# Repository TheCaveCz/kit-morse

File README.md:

# Morseovka

## Česky

Stavebnice morseovky. Zmáčkni tlačítko a pošli zprávu na druhý konec drátu.

* [Návod na stavbu](doc/manual-cz.md) ([PDF](doc/manual-cz.pdf))

## English

Coming soon...

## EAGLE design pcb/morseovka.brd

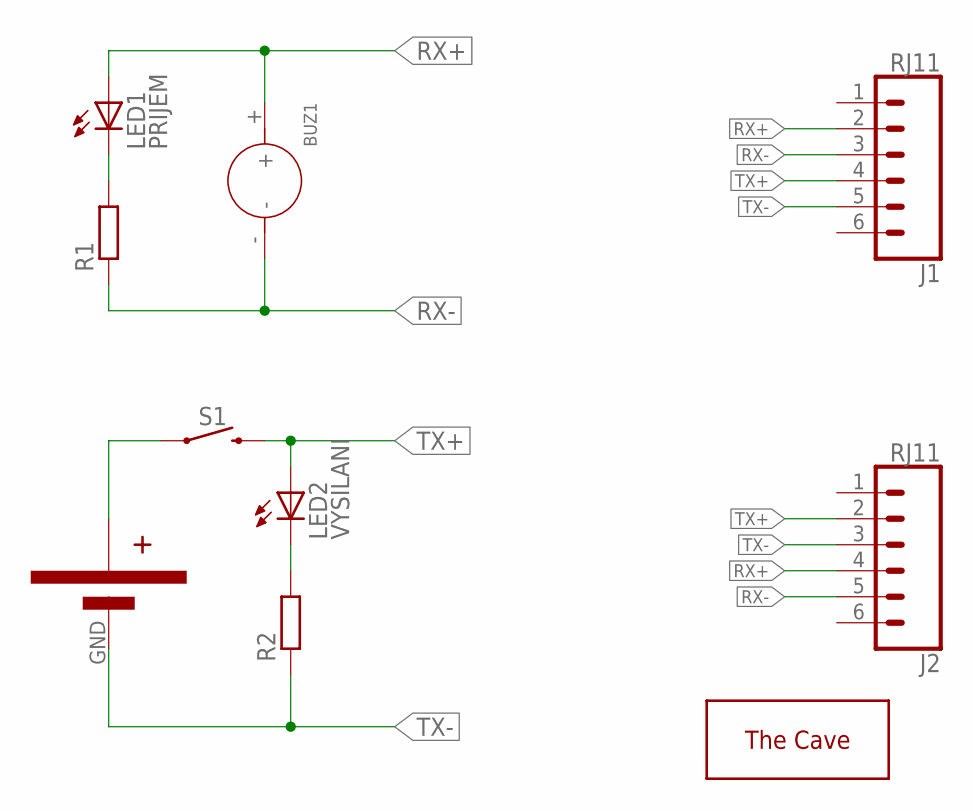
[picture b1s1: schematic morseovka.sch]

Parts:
BUZ1: DIP-BUZZER-3V(KS-12065D03YA); BZ2-7.6-D12.0XH6.5MM
J1, J2: RJ11; RJ11-6
LED1: PRIJEM; LED5MM
LED2: VYSILANI; LED5MM
R1, R2: R-EU_0207/7; 0207/7
S1: MOMENTARY-SWITCH-SPST-PTH-12MM; TACTILE_SWITCH_PTH_12MM
U$1: CR2032HSMD; CR2032H
U$2: THECAVE_LOGO_NEW_TOP; NEW_LOGO_TOP

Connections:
unnamed: LED1.K (C), R1.2
unnamed: S1.1, U$1.VCC.1 (VCC), U$1.VCC.2 (VCC)
unnamed: LED2.K (C), R2.2
RX+: BUZ1.+, J1.2, J2.4, LED1.A
RX-: BUZ1.-, J1.3, J2.5, R1.1
TX+: J1.4, J2.2, LED2.A, S1.3 (2)
TX-: J1.5, J2.3, R2.1, U$1.GND

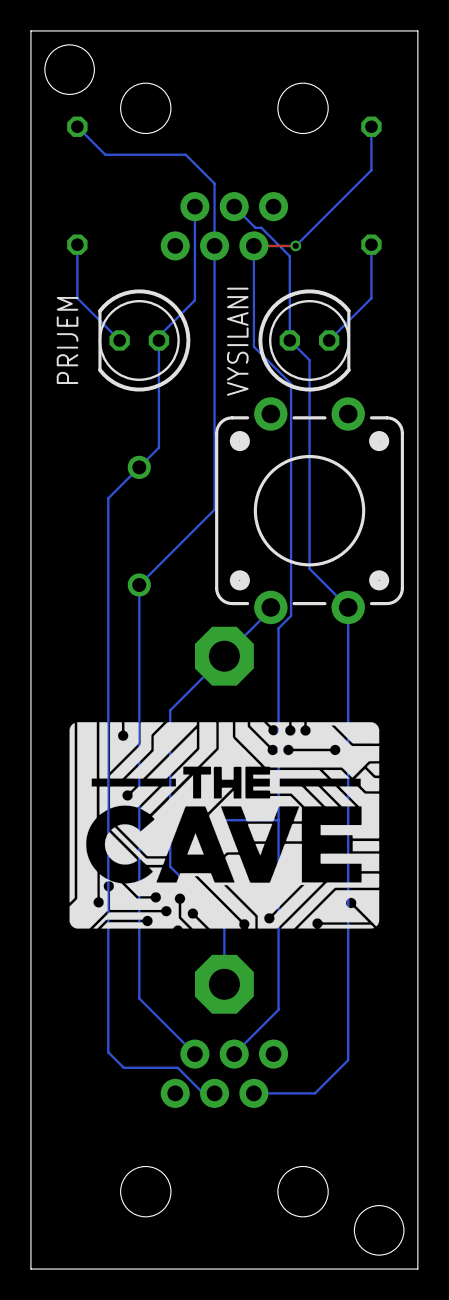
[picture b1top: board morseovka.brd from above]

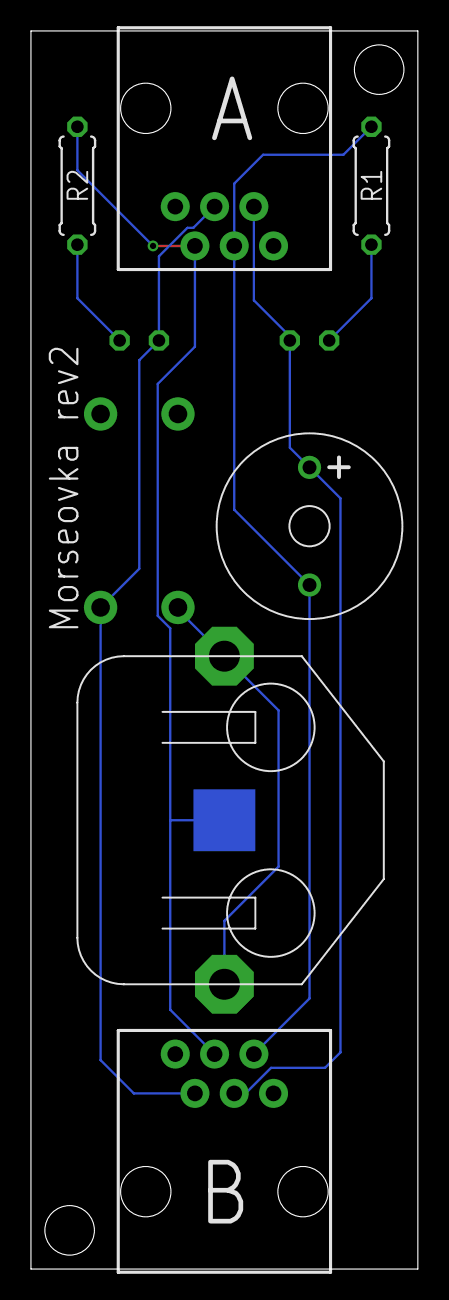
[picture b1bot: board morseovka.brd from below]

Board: 2 copper layers, 25.0 x 80.0 mm, 10 parts (6 on the bottom side), 7 nets.

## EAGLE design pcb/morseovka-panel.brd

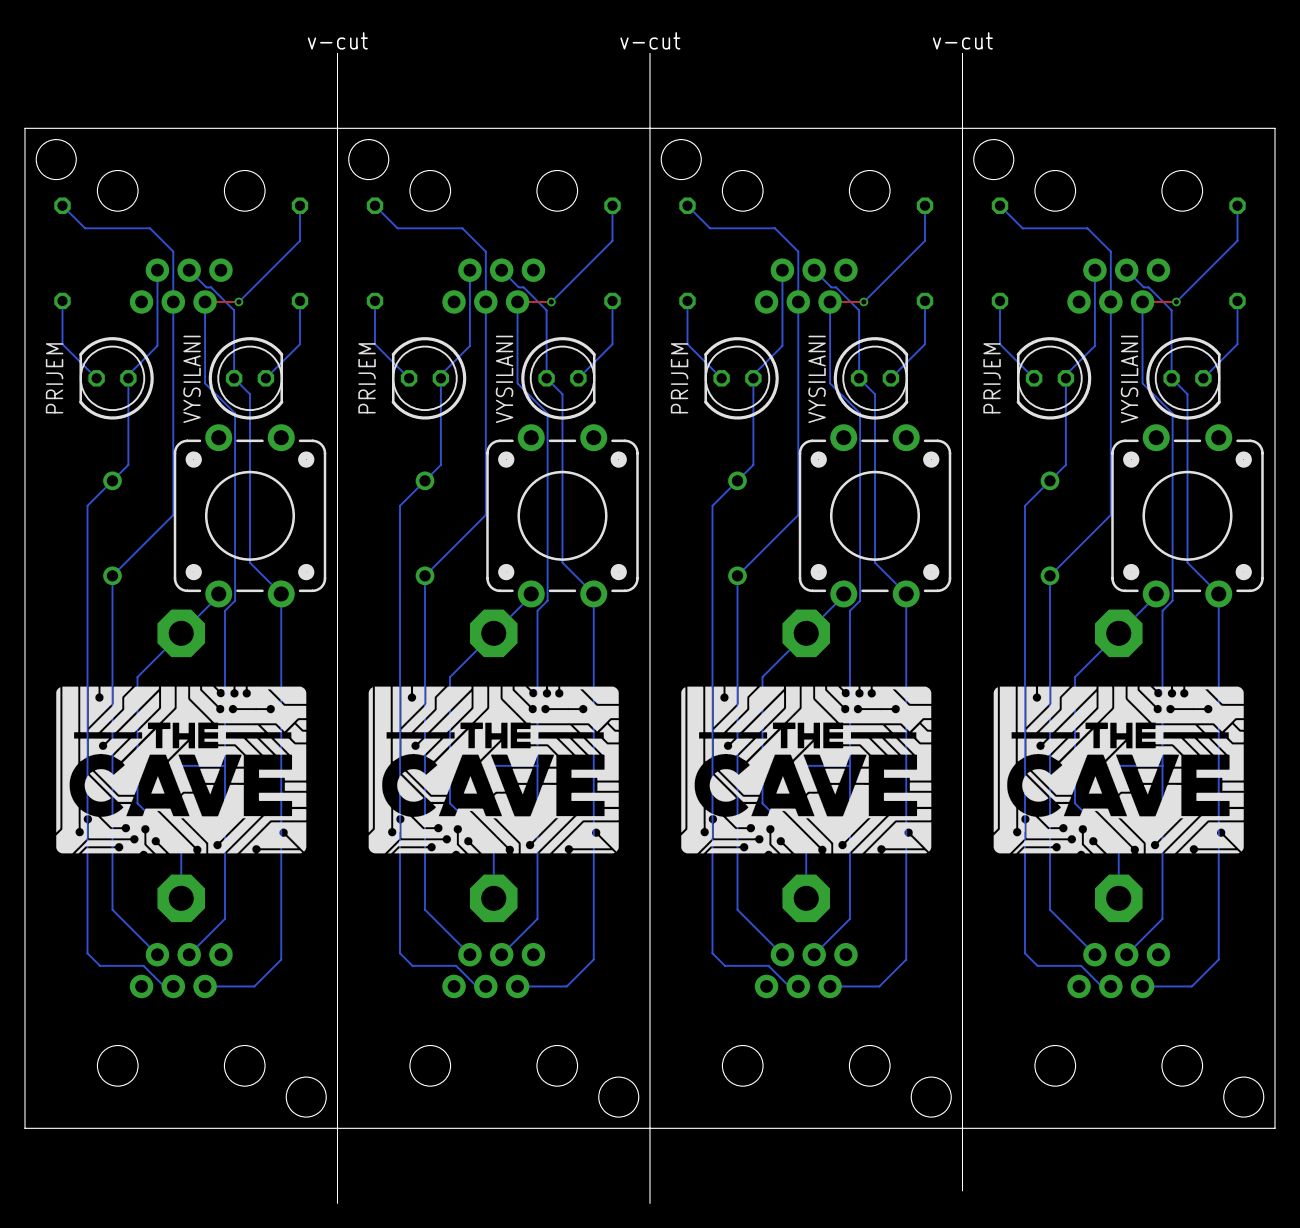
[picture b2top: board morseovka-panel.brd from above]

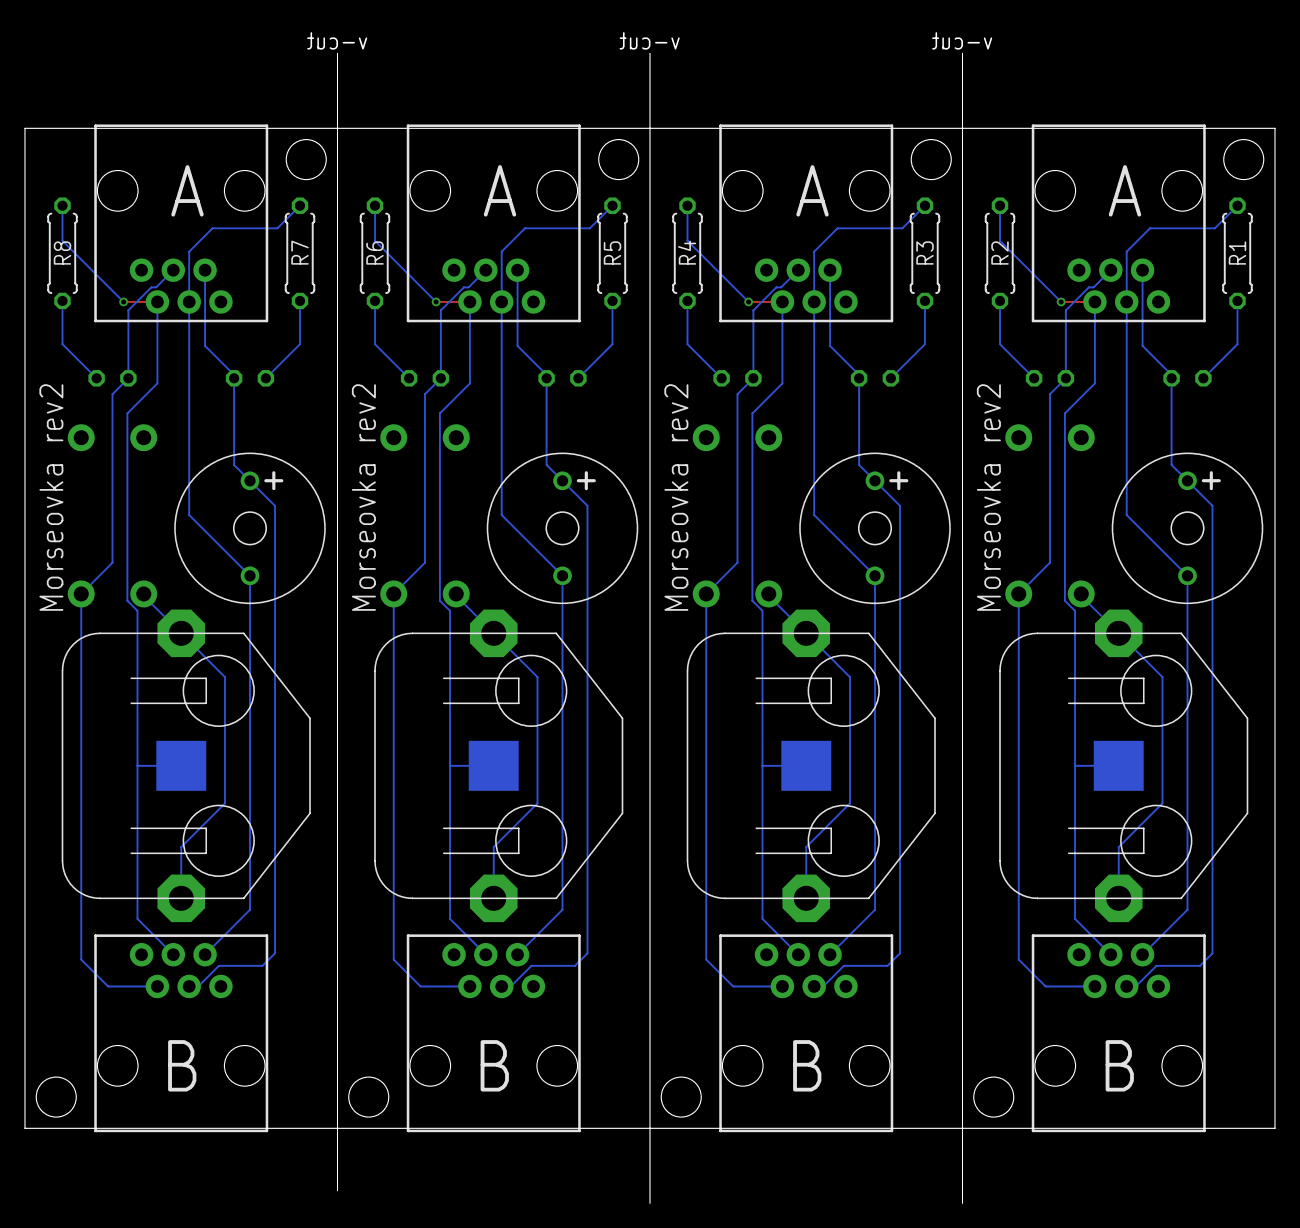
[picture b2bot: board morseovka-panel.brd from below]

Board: 2 copper layers, 100.0 x 94.3 mm, 40 parts (24 on the bottom side), 28 nets.

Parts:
BUZ1, BUZ2, BUZ3, BUZ4: BZ2-7.6-D12.0XH6.5MM
J1, J2, J3, J4, J5, J6, J7, J8: RJ11; RJ11-6
LED1, LED3, LED5, LED7: PRIJEM; LED5MM
LED2, LED4, LED6, LED8: VYSILANI; LED5MM
R1, R2, R3, R4, R5, R6, R7, R8: 0207/7
S1, S2, S3, S4: TACTILE_SWITCH_PTH_12MM
U$1, U$3, U$5, U$7: CR2032HSMD; CR2032H
U$2, U$4, U$6, U$8: THECAVE_LOGO_NEW_TOP; NEW_LOGO_TOP

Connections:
unnamed: LED1.K, R1.2
unnamed: S1.1, U$1.VCC.1, U$1.VCC.2
unnamed: LED3.K, R3.2
unnamed: LED2.K, R2.2
unnamed: LED4.K, R4.2
unnamed: S2.1, U$3.VCC.1, U$3.VCC.2
unnamed: LED5.K, R5.2
unnamed: LED6.K, R6.2
unnamed: S3.1, U$5.VCC.1, U$5.VCC.2
unnamed: LED7.K, R7.2
unnamed: LED8.K, R8.2
unnamed: S4.1, U$7.VCC.1, U$7.VCC.2
RX+: BUZ1.+, J1.2, J2.4, LED1.A
RX+1: BUZ2.+, J3.4, J4.2, LED3.A
RX+2: BUZ3.+, J5.4, J6.2, LED5.A
RX+3: BUZ4.+, J7.4, J8.2, LED7.A
RX-: BUZ1.-, J1.3, J2.5, R1.1
RX-1: BUZ2.-, J3.5, J4.3, R3.1
RX-2: BUZ3.-, J5.5, J6.3, R5.1
RX-3: BUZ4.-, J7.5, J8.3, R7.1
TX+: J1.4, J2.2, LED2.A, S1.3
TX+1: J3.2, J4.4, LED4.A, S2.3
TX+2: J5.2, J6.4, LED6.A, S3.3
TX+3: J7.2, J8.4, LED8.A, S4.3
TX-: J1.5, J2.3, R2.1, U$1.GND
TX-1: J3.3, J4.5, R4.1, U$3.GND
TX-2: J5.3, J6.5, R6.1, U$5.GND
TX-3: J7.3, J8.5, R8.1, U$7.GND

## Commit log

2019-06-20 Add manual and pcbs
2019-06-23 Fixed typo

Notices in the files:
parts and their libraries:
SparkFun-Switches: Licensing: Creative Commons ShareAlike 4.0 International - https://creativecommons.org/licenses/by-sa/4.0
